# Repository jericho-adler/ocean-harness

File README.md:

# Ocean Harness

An ADAS CAN interposer for the **Fisker Ocean**, designed in KiCad. It plugs in between the car's harness and the ADAS ECU's main connector (CON1), so a comma device can sit between the car and the ECU. When the board has no power it drops back to a plain hard-wired passthrough, and the car behaves exactly as stock.

| | |
| --- | --- |
| Board | 89.0 × 72.2 mm, 4 layers, every part on the top side |
| Parts | 30 components, plus two M3 mounting holes and three fiducials |
| Mounting | One M3 hole in each gap between the stacked headers |
| Power | Taken from the harness VBAT on J3 pin 1. No external supply |
| Comma link | USB-C (J1) carrying 12 V and CAN, comma "OBD-C" style. It's not a USB data port |
| Revision | Rev 2, November 2026. New layout, not yet built |

## Connectors

| Ref | Part | Side | Carries |
| --- | --- | --- | --- |
| J3 | Molex 0346910200, 20-way | Vehicle harness | CON1 section A |
| J5 | Molex 0346910162, 16-way | Vehicle harness | CON1 section B |
| J4 | Molex 0346910200, 20-way | ADAS ECU | CON1 section A |
| J6 | Molex 0346910162, 16-way | ADAS ECU | CON1 section B |
| J1 | JAE DX07S024XJ1R1100, USB-C | Comma device | 12 V, three CAN pairs, one control line |

The harness side is on the right edge ("CAR HARNESS-->") and the ECU side is on the left ("<--ADAS ECU"). 22 of the 36 CON1 circuits are carried. Every other pin is left unconnected.

## How it works

### Power

VBAT comes in on J3 pin 1. It goes straight through to J4 pin 1 (1.6 mm leaving J3, 2.4 mm along B.Cu, 2.0 mm into J4, with six 0.4 mm vias at the layer change), so the ECU keeps its own supply whatever the board is doing.

The board takes its own power from the same feed through F1 (Bel 0685T3000-01, 3 A time-lag, 63 V), so a short anywhere on the board side opens F1 rather than the car's fuse for the ECU. `VBAT_FUSED` then goes to Q1 (Diodes DMP4015SSS-13 P-channel MOSFET), which blocks reverse polarity into the `12V_PROT` rail. D9 and D11 (two SMAJ16A) clamp transients on that rail, and C1 decouples it. `12V_PROT` powers the comma device through all four USB-C VBUS pins.

Q1 is wired drain-to-input, source-to-output, so its body diode conducts battery-to-load and the channel then shorts it out. R7 (100 kΩ) pulls the gate to ground, which holds the FET hard on whenever `12V_PROT` is up; under reversed polarity the source collapses with it, V<sub>GS</sub> goes to zero and the FET — and its body diode — both block. D15 (BZT52C16, 16 V zener) clamps V<sub>GS</sub>: without it the gate would sit at the full battery voltage and exceed the ±25 V rating when D9/D11 clamp a transient at around 26 V.

At 11 mΩ this drops 0.1 W at the 3 A fuse limit, against 1.5 W for the SS34 Schottky it replaces, and hands about 0.4 V of headroom back to the comma device.

R5 (160 Ω) drops about 2 V from `12V_PROT` to make `VIN`, which runs the relay coil. That holds the coil near its 12 V rating on a 14 V running rail. CR1 (1N4148W) is the coil's flyback diode, and C2 decouples `VIN`.

The analog switches get their own clamped supply. `VIN` runs through D12 (DSK14) and R6 (3.3 kΩ) to `SW_VCC`, where D13 (BZT52C12) holds it to about 12 V and C3 decouples it. `SW_VCC` feeds both V+ and VL on U1 and U2. This clamp is the one used on the Volvo/Polestar harness box, and rev 2 added it for three reasons:

- The DG419LE is rated for a 3 to 16 V supply (18 V absolute max). The SMAJ16A clamps don't start conducting until 17.8 V, so without D13 the switches could sit outside their rating on a high input.
- D12 stops current back-feeding into `VIN` through the switches' internal clamp diodes when the board is unpowered but the car bus is live.
- R6 keeps the standby draw to about 0.6 mA at 14.4 V.

### The CAN intercept

K1 (Omron G5V-2-H1 DC12, DPDT) switches the vehicle's ADAS CAN (HSCAN1, J3 pins 19/20). Its common contacts are on the vehicle side and its normally-closed contacts go to the ECU, so with no power the car and ECU are hard-wired together and the comma device is out of the loop.

Once the board has power, the relay moves the vehicle side over to the comma device's `_C` pair (J1 A2/A3). The ECU stays wired to the device's `_MOD` pair (J1 B2/B3), so the device has the car on one port and the ECU on the other. The coil is energized the whole time the board has power. The `-H1` variant is used for its 150 mW coil (against 500 mW for the standard part) and its 21.6 V maximum coil voltage.

U1 and U2 (Vishay DG419LE SPDT analog switches) decide what happens between the two segments. The comma device controls them through `SBU 1` on J1 A8.

With `SBU 1` low, the switches bridge `_C` to `_MOD`, so the car and ECU stay connected and the device only listens. That's the default: R2 + R3 form a 240 Ω pulldown, so it's also the safe state if the device never drives the pin.

With `SBU 1` high, the bridge opens and R4 (120 Ω) is switched across the ECU-side pair, so that segment keeps its own termination. The device is now fully in the middle.

| Power | `SBU 1` | Car ↔ ECU | Comma device |
| --- | --- | --- | --- |
| Off | Any | Connected through K1's normally-closed contacts | Isolated |
| On | Low | Connected through U1/U2 | Listening on both segments |
| On | High | Cut. The ECU segment is terminated by R4 | In the middle |

### Straight passthrough

These run between the harness and ECU connectors untouched:

- the four corner-radar CAN-FD pairs (CMRR FR, RR, FL, RL)
- the DMS LED drive
- all six ultrasonic sensor lines (power, power return and signal for USS1 and USS2)
- ground on pin 14

The mid-range radar CAN (MRR) also passes straight through. It has a passive stub tap to J1 A10/A11 so the device can monitor it.

### Protection

Four PESD1CAN ESD arrays protect:

- D3, the vehicle-side ADAS CAN
- D2, the ECU-side ADAS CAN
- D8, the MRR tap
- D1, the `_C` pair (J1 A2/A3), next to J1

D14 (PESD24VS1UB) protects `SBU 1`. The reserved `COMMA_P`/`COMMA_N` pair has no ESD diode now that D1 has moved.

F1 fuses the board's tap off VBAT. Reverse polarity and transients on the supply are handled by Q1, D9 and D11 as described above.

## Pinouts

### J1 (USB-C to the comma device)

| Pin | USB-C name | Signal | Use |
| --- | --- | --- | --- |
| A4, A9, B4, B9 | VBUS | `12V_PROT` | 12 V supply to the device |
| A1, A12, B1, B12, shell | GND | GND | |
| A2 / A3 | TX1+ / TX1- | `ADAS_CAN_H_C` / `ADAS_CAN_L_C` | Car side of the intercepted ADAS CAN, live when the relay is energized |
| B2 / B3 | TX2+ / TX2- | `ADAS_CAN_H_MOD` / `ADAS_CAN_L_MOD` | ECU side of the intercepted ADAS CAN |
| A11 / A10 | RX2+ / RX2- | `MRR_CAN_H` / `MRR_CAN_L` | Listen-only tap on the mid-range radar CAN |
| B11 / B10 | RX1+ / RX1- | `COMMA_P` / `COMMA_N` | Wired only to J1. Reserved |
| A8 | SBU1 | `SBU 1` | Switch control input |
| A5, B5, A6, A7, B6, B7, B8 | CC, D+/D-, SBU2 | | Not connected |

### J3 ↔ J4 (CON1 section A, 20-way)

| Pin | Signal | Path |
| --- | --- | --- |
| 1 | VBAT (`Harness_12v`) | Straight through, and powers the board through F1 and Q1 |
| 6 | `USS2_PWR` | Straight through |
| 7 | `USS1_PWR` | Straight through |
| 14 | GND | Straight through, and board ground |
| 15 | `USS1_PWR_N` | Straight through |
| 16 | `USS1_Signal` | Straight through |
| 17 | `USS2_Signal` | Straight through |
| 18 | `USS2_PWR_N` | Straight through |
| 19 / 20 | ADAS CAN L / H | Intercepted through K1. `ADAS_CAN` on J3, `ADAS_CAN_MOD` on J4 |

### J5 ↔ J6 (CON1 section B, 16-way)

| Pin | Signal | Path |
| --- | --- | --- |
| 1 / 9 | MRR CAN L / H | Straight through, tapped to J1 A10/A11 |
| 2 / 3 | CMRR FR CAN H / L | Straight through |
| 4 / 5 | CMRR RR CAN H / L | Straight through |
| 10 / 11 | CMRR FL CAN H / L | Straight through |
| 12 / 13 | CMRR RL CAN H / L | Straight through |
| 15 / 16 | DMS LED1 L / H | Straight through |

## Board construction

| Layer | Use |
| --- | --- |
| F.Cu | Signals, GND pour |
| In1.Cu | Solid GND plane |
| In2.Cu | Solid GND plane, with a `12V_PROT` island under J1, C1 and D9 to D11 and a 0.3 mm `VIN` link from R5 to K1 |
| B.Cu | Signals, GND pour |

The two header pairs face out of opposite edges, so the J5↔J6 pin order is reversed. Those 12 nets cross over in the strip between the headers. The six ultrasonic lines run on B.Cu around J4. Signal tracks are 0.25 mm with 45° bends. The DMS LED drive is 0.6 mm, necked to 0.35 mm where it threads between connector pins and past two CAN vias. The VBAT passthrough leaves J3 on B.Cu at 1.6 mm (squeezed between the J3 mounting peg and the board edge), runs up the right side and across the top at 2.4 mm, and drops to F.Cu through six 0.4 mm vias for the last 2.0 mm run into J4. F1, Q1, D15 and R7 all sit in the gap between J5 and J3, in that order along the strip, and F1 is fed from that trunk through three vias. `VBAT_FUSED` is just the 6 mm hop from F1 to Q1's drain pads, so almost nothing on the board is upstream of the reverse-polarity FET. `12V_PROT` leaves Q1's source pads, drops below J3 and runs the length of the right edge on a 1.2 mm F.Cu track, across the bottom, and up through the slot where D10 used to be to reach D11, D9, C1 and R5. From C1 it continues through the In2 island, which connects solid to the VBUS pins. `VIN` gets from R5 to K1 on a 0.3 mm In2 track, because both outer layers are crossed by other traces there.

## Repository layout

| Path | Contents |
| --- | --- |
| `PCB Files/` | KiCad 10 project (`.kicad_pro`, `.kicad_sch`, `.kicad_pcb`) and design reviews |
| `images/` | Iso render |
| `3D models/` | STEP model. Still shows the rev 1 layout |

## License

Licensed under the [CERN Open Hardware Licence Version 2 - Strongly Reciprocal](LICENSE) (CERN-OHL-S-2.0).

## Disclaimer

This is a community hardware design shared as-is, with no warranty. It's designed for the Fisker Ocean only, and using it on other platforms is unverified. **Use at your own risk.**

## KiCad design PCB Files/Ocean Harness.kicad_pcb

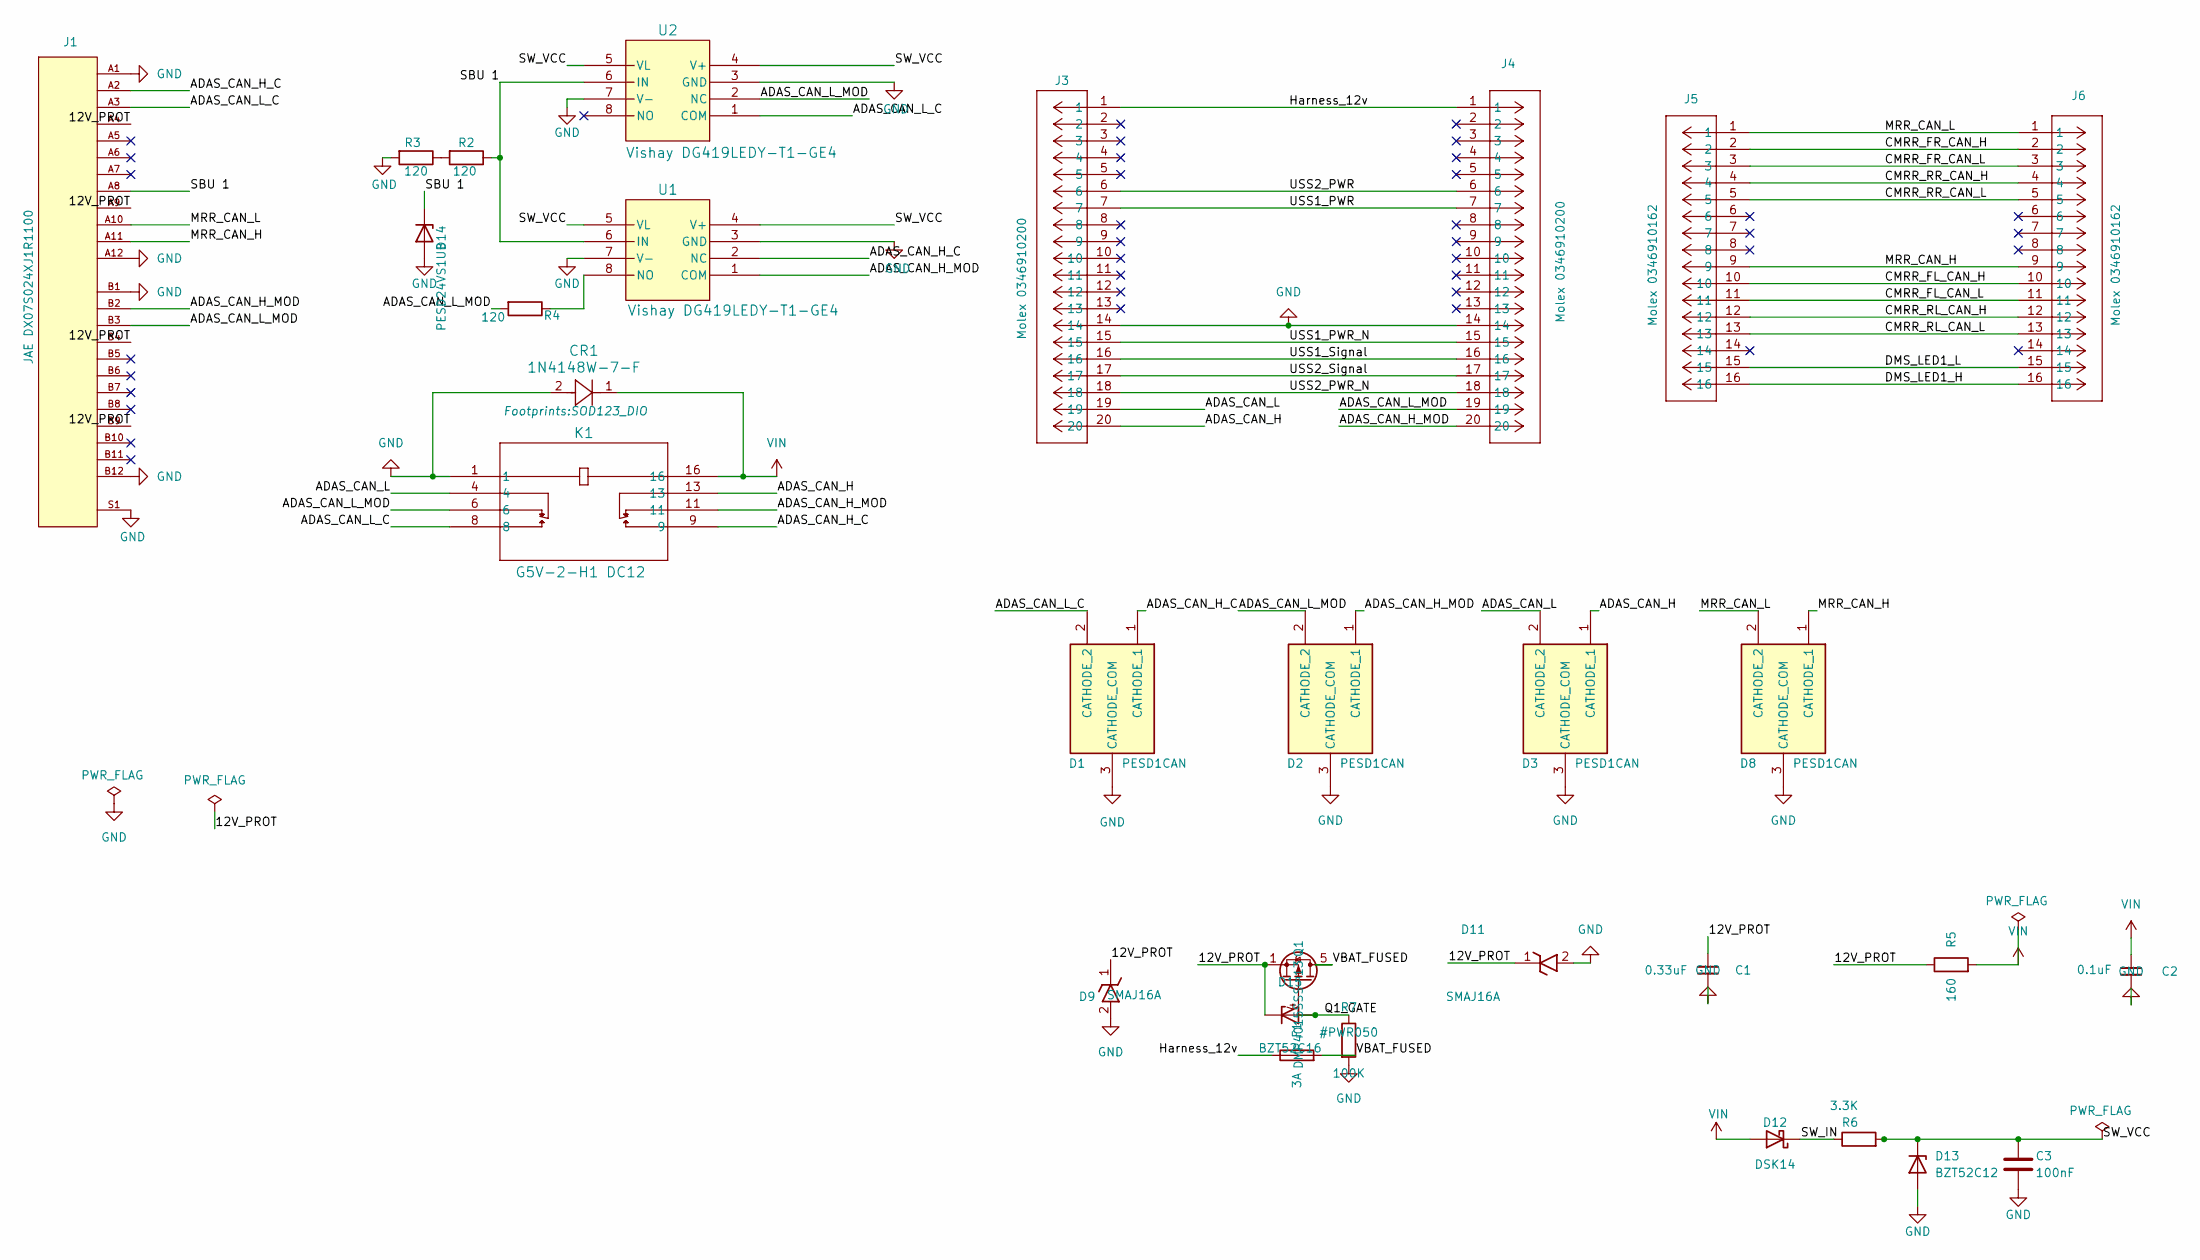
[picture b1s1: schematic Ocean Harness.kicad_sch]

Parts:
C1: 0.33uF; C_0603_1608Metric; Voltage 50V; MPN TCC0603X7R334K500CT; JLCPCB Part # C282682
C2: 0.1uF; C_0603_1608Metric; Voltage 50V; MPN CL10B104KB8NNNC; JLCPCB Part # C1591
C3: 100nF; C_0603_1608Metric; MPN CL10B104KB8NNNC; JLCPCB Part # C1591
CR1: 1N4148W-7-F; SOD123_DIO; MPN 1N4148W-7-F; JLCPCB Part # C83528
D1, D2, D3, D8: PESD1CAN; MPN PESD1CAN,215; JLCPCB Part # C15771
D9, D11: SMAJ16A; MPN SMAJ16A; JLCPCB Part # C74561
D12: DSK14; D_SOD-123F; MPN DSK14; JLCPCB Part # C37049
D13: BZT52C12; SOD123_DIO; MPN BZT52C12-7-F; JLCPCB Part # C124196
D14: PESD24VS1UB; D_SOD-523; MPN PESD24VS1UB,115; JLCPCB Part # C85382
D15: BZT52C16; SOD123_DIO; MPN BZT52C16-7-F; JLCPCB Part # C397929
F1: 3A; Fuse_1206_3216Metric; MPN 0685T3000-01; JLCPCB Part # C5456894
J1: JAE DX07S024XJ1R1100; MPN DX07S024XJ1R1100; JLCPCB Part # C134113
J3, J4: Molex 0346910200; CONN_SD-34691-100_20_MOL; MPN 34691-0200; JLCPCB Part # C293461
J5, J6: Molex 0346910162; CONN_SD-34691-100_16_MOL; MPN 34691-0162; JLCPCB Part # C585844
K1: G5V-2-H1 DC12; Omron G5V-2-DC12; MPN G5V-2-H1 DC12; JLCPCB Part # C128021
Q1: DMP4015SSS-13; SOIC-8_3.9x4.9mm_P1.27mm; MPN DMP4015SSS-13; JLCPCB Part # C508210
R2, R3, R4: 120; Rohm ESR03EZPJ121; MPN ESR03EZPJ121; JLCPCB Part # C2846664
R5: 160; R_0805_2012Metric; MPN FRC0805F1600TS; JLCPCB Part # C2960793
R6: 3.3K; Rohm ESR03EZPJ121; MPN ESR03EZPF3301; JLCPCB Part # C510091
R7: 100K; Rohm ESR03EZPJ104; MPN ESR03EZPJ104; JLCPCB Part # C253331
U1, U2: Vishay DG419LEDY-T1-GE4; MPN DG419LEDY-T1-GE4; JLCPCB Part # C2673265

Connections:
/12V_PROT: C1.1, D9.1, D11.1, D15.1 (K), J1.A4, J1.A9, J1.B4, J1.B9, Q1.1 (S), Q1.2 (S), Q1.3 (S), R5.1
/ADAS_CAN_H: D3.1 (CATHODE_1), J3.20, K1.13
/ADAS_CAN_H_C: D1.1 (CATHODE_1), J1.A2, K1.9, U1.2 (NC)
/ADAS_CAN_H_MOD: D2.1 (CATHODE_1), J1.B2, J4.20, K1.11, U1.1 (COM)
/ADAS_CAN_L: D3.2 (CATHODE_2), J3.19, K1.4
/ADAS_CAN_L_C: D1.2 (CATHODE_2), J1.A3, K1.8, U2.1 (COM)
/ADAS_CAN_L_MOD: D2.2 (CATHODE_2), J1.B3, J4.19, K1.6, R4.2, U2.2 (NC)
/CMRR_FL_CAN_H: J5.10, J6.10
/CMRR_FL_CAN_L: J5.11, J6.11
/CMRR_FR_CAN_H: J5.2, J6.2
/CMRR_FR_CAN_L: J5.3, J6.3
/CMRR_RL_CAN_H: J5.12, J6.12
/CMRR_RL_CAN_L: J5.13, J6.13
/CMRR_RR_CAN_H: J5.4, J6.4
/CMRR_RR_CAN_L: J5.5, J6.5
/DMS_LED1_H: J5.16, J6.16
/DMS_LED1_L: J5.15, J6.15
/Harness_12v: F1.1, J3.1, J4.1
/MRR_CAN_H: D8.1 (CATHODE_1), J1.A11, J5.9, J6.9
/MRR_CAN_L: D8.2 (CATHODE_2), J1.A10, J5.1, J6.1
/Q1_GATE: D15.2 (A), Q1.4 (G), R7.1
/SBU 1: D14.1 (K), J1.A8, R2.1, U1.6 (IN), U2.6 (IN)
/SW_IN: D12.1 (K), R6.1
/SW_VCC: C3.1, D13.1 (K), R6.2, U1.4 (V+), U1.5 (VL), U2.4 (V+), U2.5 (VL)
/USS1_PWR: J3.7, J4.7
/USS1_PWR_N: J3.15, J4.15
/USS1_Signal: J3.16, J4.16
/USS2_PWR: J3.6, J4.6
/USS2_PWR_N: J3.18, J4.18
/USS2_Signal: J3.17, J4.17
/VBAT_FUSED: F1.2, Q1.5 (D), Q1.6 (D), Q1.7 (D), Q1.8 (D)
GND: C1.2, C2.2, C3.2, CR1.2, D1.3 (CATHODE_COM), D2.3 (CATHODE_COM), D3.3 (CATHODE_COM), D8.3 (CATHODE_COM), D9.2, D11.2, D13.2 (A), D14.2 (A), J1.A1, J1.A12, J1.B1, J1.B12, J1.S1, J3.14, J4.14, K1.1, R3.2, R7.2, U1.3 (GND), U1.7 (V-), U2.3 (GND), U2.7 (V-)
unnamed: R2.2, R3.1
unnamed: R4.1, U1.8 (NO)
VIN: C2.1, CR1.1, D12.2 (A), K1.16, R5.2

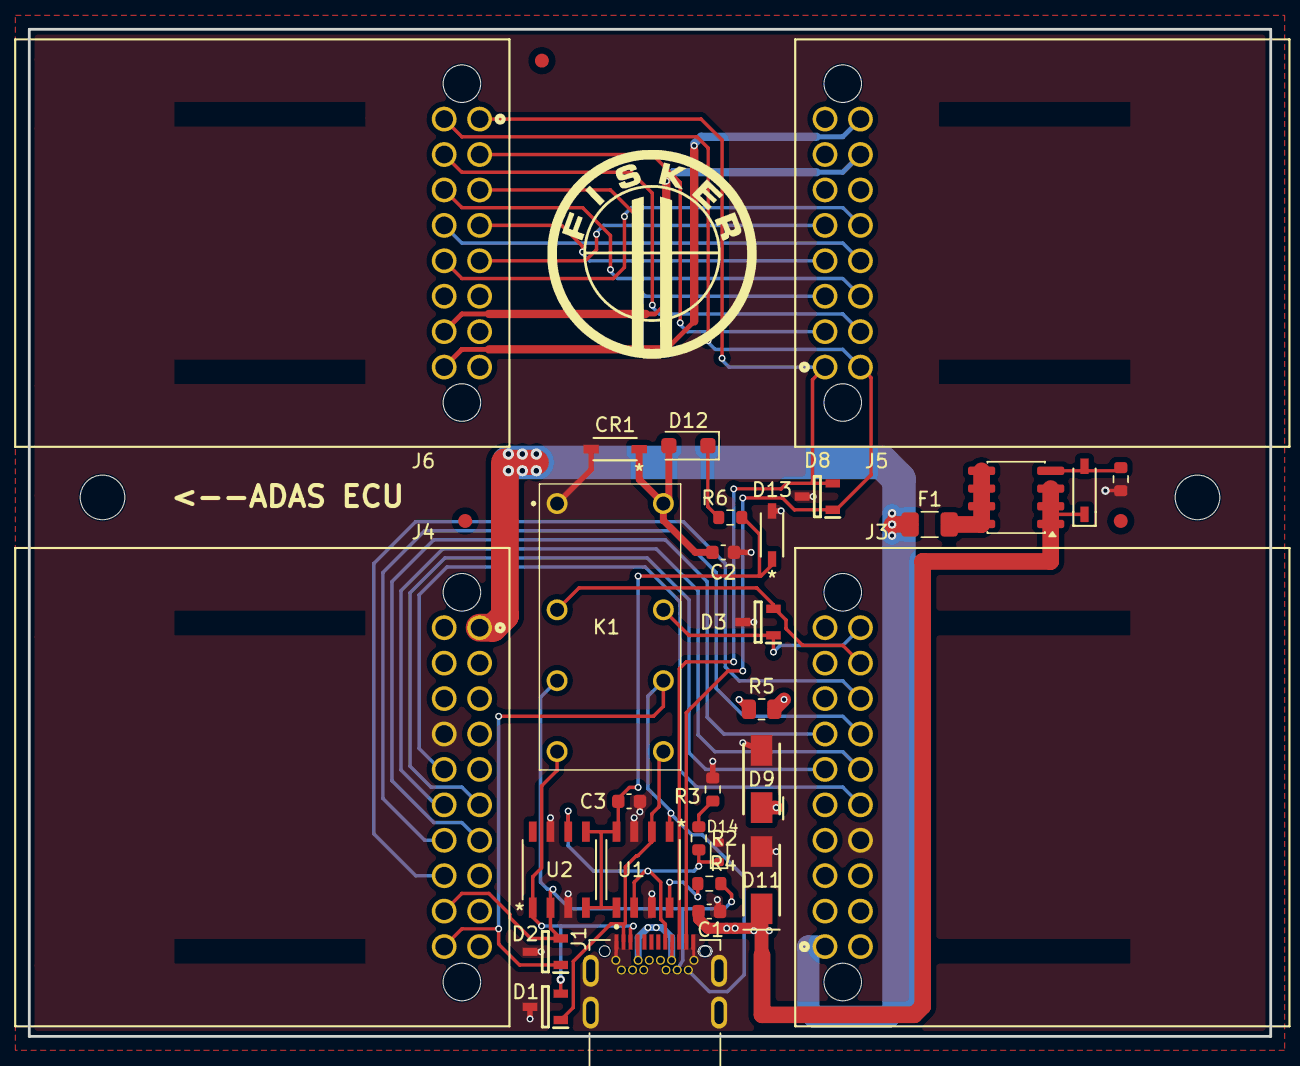
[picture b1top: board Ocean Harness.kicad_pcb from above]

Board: 4 copper layers, 89.0 x 72.2 mm, 35 parts (0 on the bottom side), 35 nets.

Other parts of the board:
FID1, FID2, FID3: Fiducial_1mm_Mask2mm
H1, H2: MountingHole_3.2mm_M3
